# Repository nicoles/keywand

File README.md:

# keywand
 Key of the Star, with powers burning bright, reveal the staff and shine your light. RELEASE!

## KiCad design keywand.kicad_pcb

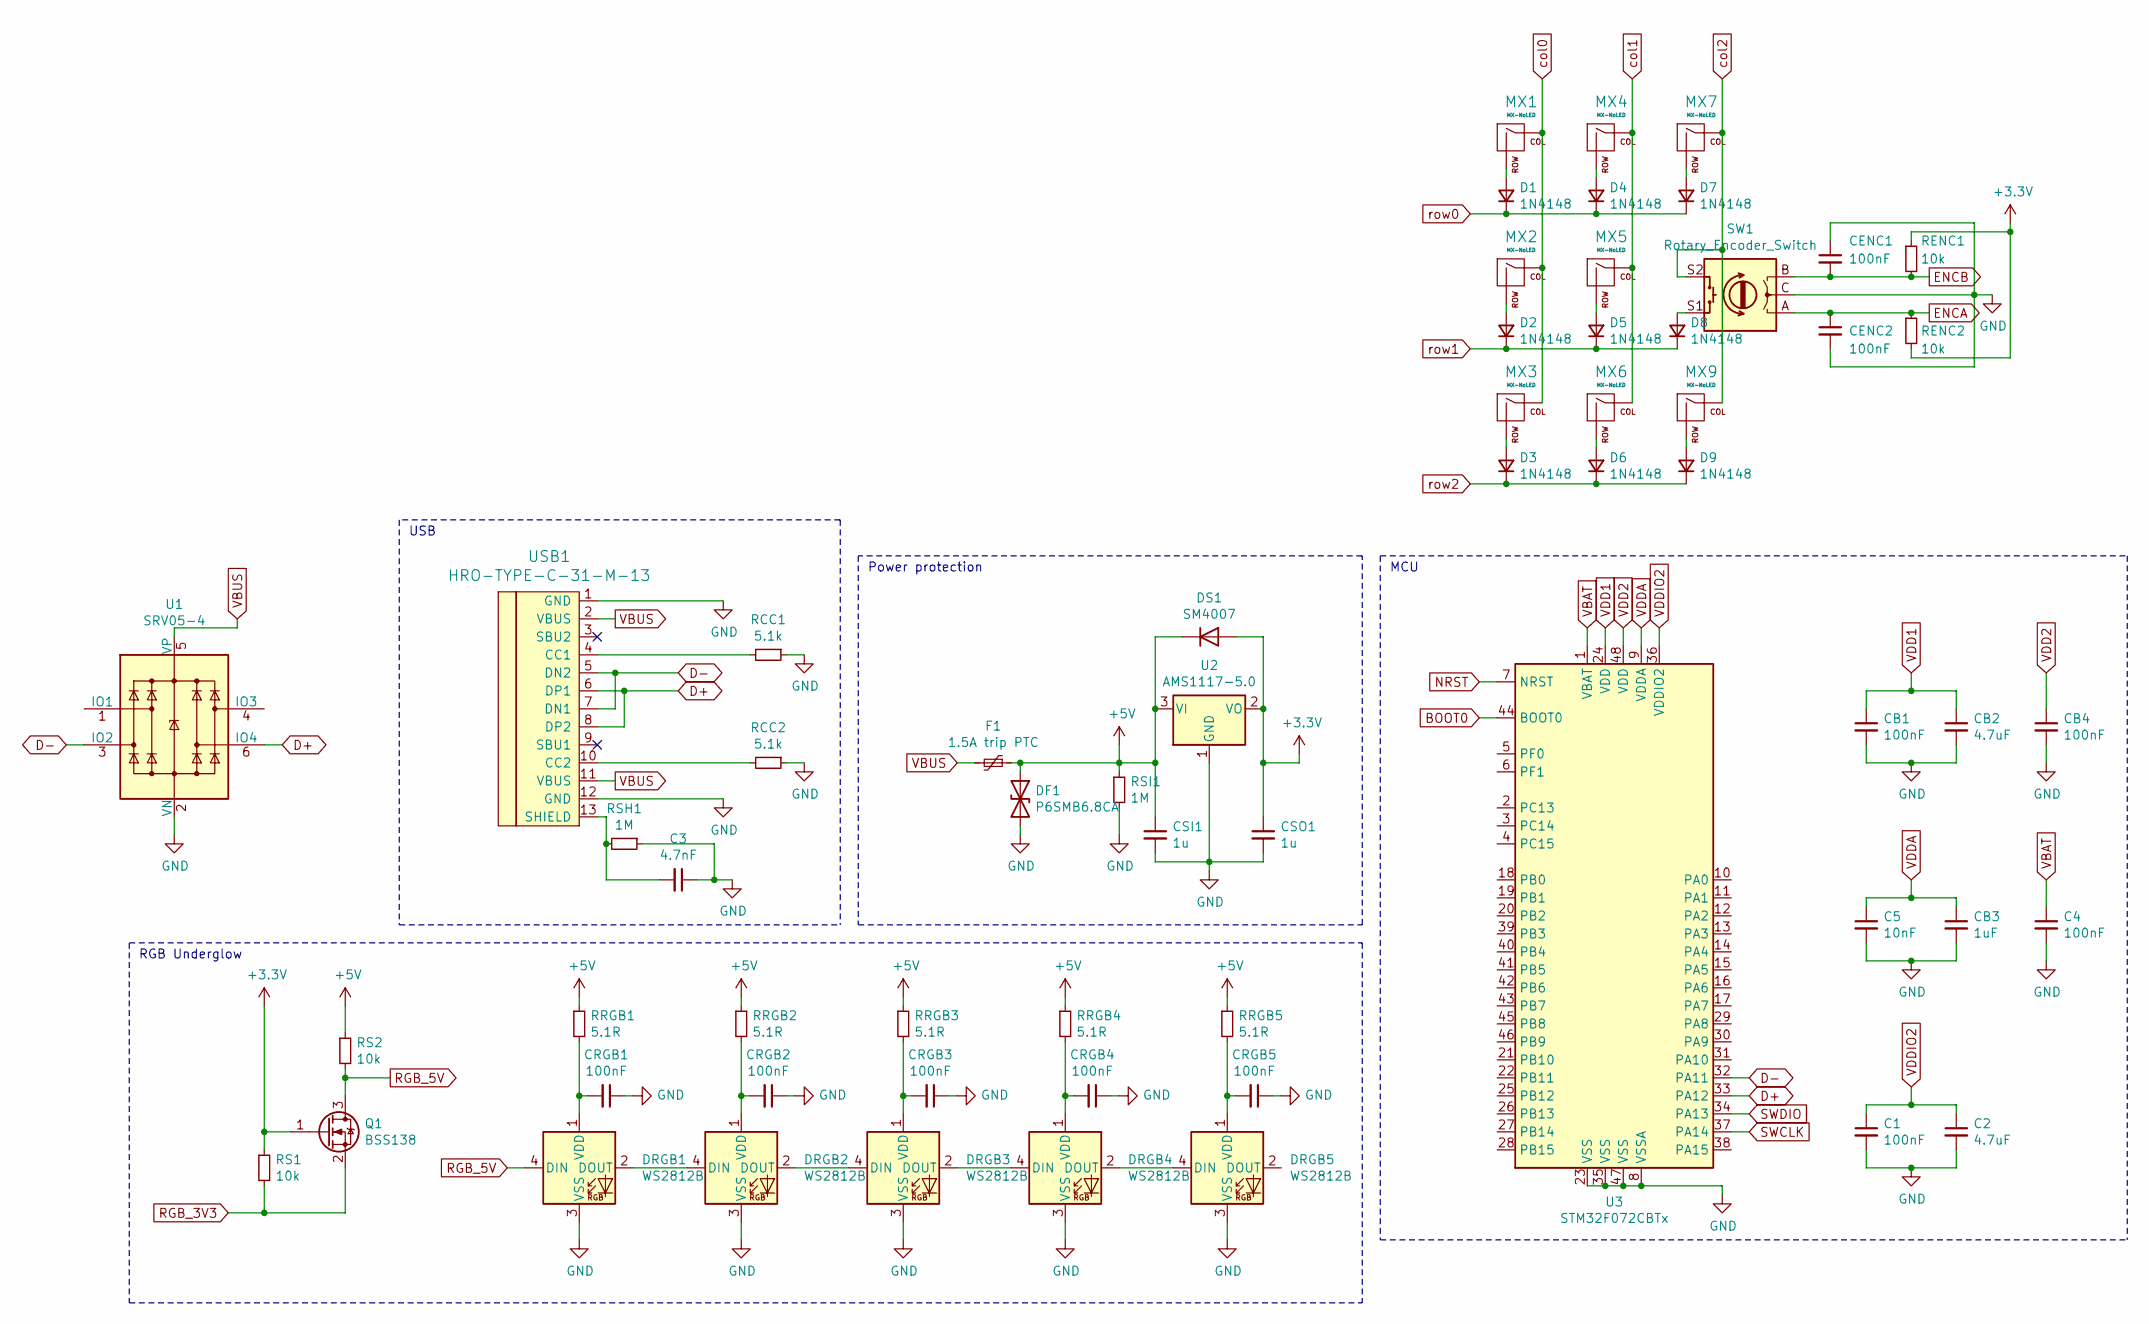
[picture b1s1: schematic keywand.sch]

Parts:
C1, C4: 100nF; C_0402_1005Metric; LCSC C1525
C2: 4.7uF; C_0402_1005Metric; LCSC C23733
C3: 4.7nF; C_0603_1608Metric; LCSC C53987
C5: 10nF; C_0402_1005Metric; LCSC C15195
CB1, CB4: 100nF; C_0402_1005Metric; LCSC C1525
CB2: 4.7uF; C_0402_1005Metric; LCSC C23733
CB3: 1uF; C_0402_1005Metric; LCSC C52923
CENC1, CENC2: 100nF; C_0603_1608Metric; LCSC C14663
CRGB1, CRGB2, CRGB3, CRGB4, CRGB5: 100nF; C_0603_1608Metric
CSI1: 1u; C_0805_2012Metric; JLCCode C28323
CSO1: 1u; C_0805_2012Metric; JLCCode C28323
D1, D2, D3, D4, D5, D6, D7, D8, D9: 1N4148; D_SOD-123; LCSC C81598
DF1: P6SMB6.8CA; D_SMB; JLCCode C78395
DRGB1, DRGB2, DRGB3, DRGB4, DRGB5: WS2812B; LED_SK6812MINI_PLCC4_3.5x3.5mm_P1.75mm; JLCCode C114583
DS1: SM4007; D_MELF; JLCCode C64898
F1: 1.5A trip PTC; Fuse_1812_4532Metric; JLCCode C84140
MX1, MX2, MX3, MX4, MX5, MX6, MX7, MX9: MX-NoLED; MXOnly-1U-NoLED
Q1: BSS138; SOT-23; JLCCode C193019
RCC1, RCC2: 5.1k; R_0603_1608Metric
RENC1, RENC2: 10k; C_0603_1608Metric; LCSC C25804
RRGB1, RRGB2, RRGB3, RRGB4, RRGB5: 5.1R; R_0603_1608Metric; JLCCode C25197
RS1, RS2: 10k; R_1206_3216Metric; JLCCode C17902
RSH1: 1M; R_0603_1608Metric
RSI1: 1M; C_0603_1608Metric; JLCCode C22935
SW1: Rotary_Encoder_Switch; RotaryEncoder_Alps_EC12E-Switch_Vertical_H20mm
U1: SRV05-4; SOT-23-6; LCSC C85364
U2: AMS1117-5.0; SOT-223-3_TabPin2; JLCCode C6187
U3: STM32F072CBTx; LQFP-48_7x7mm_P0.5mm
USB1: HRO-TYPE-C-31-M-13; LCSC C223906

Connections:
+3V3: CSO1.1, DS1.2 (A), Q1.1 (G), RENC1.1, RENC2.2, RS1.1, U2.2 (VO)
+5V: CSI1.1, DF1.1 (A1), DS1.1 (K), F1.1, RRGB1.1, RRGB2.1, RRGB3.1, RRGB4.1, RRGB5.1, RS2.1, RSI1.1, U2.3 (VI)
BOOT0: U3.44 (BOOT0)
D+: U1.6 (IO4), U3.33 (PA12), USB1.6 (DP1), USB1.8 (DP2)
D-: U1.3 (IO2), U3.32 (PA11), USB1.5 (DN2), USB1.7 (DN1)
ENCA: CENC2.1, RENC2.1, SW1.A
ENCB: CENC1.2, RENC1.2, SW1.B
GND: C1.2, C2.2, C3.1, C4.2, C5.2, CB1.2, CB2.2, CB3.2, CB4.2, CENC1.1, CENC2.2, CRGB1.1, CRGB2.1, CRGB3.1, CRGB4.1, CRGB5.1, CSI1.2, CSO1.2, DF1.2 (A2), DRGB1.3 (VSS), DRGB2.3 (VSS), DRGB3.3 (VSS), DRGB4.3 (VSS), DRGB5.3 (VSS), RCC1.1, RCC2.1, RSH1.1, RSI1.2, SW1.C, U1.2 (VN), U2.1 (GND), U3.8 (VSSA), U3.23 (VSS), U3.35 (VSS), U3.47 (VSS), USB1.1 (GND), USB1.12 (GND)
NRST: U3.7 (NRST)
unnamed: C3.2, RSH1.2, USB1.13 (SHIELD)
unnamed: CRGB1.2, DRGB1.1 (VDD), RRGB1.2
unnamed: CRGB2.2, DRGB2.1 (VDD), RRGB2.2
unnamed: CRGB3.2, DRGB3.1 (VDD), RRGB3.2
unnamed: CRGB4.2, DRGB4.1 (VDD), RRGB4.2
unnamed: CRGB5.2, DRGB5.1 (VDD), RRGB5.2
unnamed: D1.2 (A), MX1.2 (ROW)
unnamed: D2.2 (A), MX2.2 (ROW)
unnamed: D3.2 (A), MX3.2 (ROW)
unnamed: D4.2 (A), MX4.2 (ROW)
unnamed: D5.2 (A), MX5.2 (ROW)
unnamed: D6.2 (A), MX6.2 (ROW)
unnamed: D7.2 (A), MX7.2 (ROW)
unnamed: D8.2 (A), SW1.S1
unnamed: D9.2 (A), MX9.2 (ROW)
unnamed: DRGB1.2 (DOUT), DRGB2.4 (DIN)
unnamed: DRGB2.2 (DOUT), DRGB3.4 (DIN)
unnamed: DRGB3.2 (DOUT), DRGB4.4 (DIN)
unnamed: DRGB4.2 (DOUT), DRGB5.4 (DIN)
unnamed: RCC1.2, USB1.4 (CC1)
unnamed: RCC2.2, USB1.10 (CC2)
RGB_3V3: Q1.2 (S), RS1.2
RGB_5V: DRGB1.4 (DIN), Q1.3 (D), RS2.2
SWCLK: U3.37 (PA14)
SWDIO: U3.34 (PA13)
VBAT: C4.1, U3.1 (VBAT)
VBUS: F1.2, U1.5 (VP), USB1.2 (VBUS), USB1.11 (VBUS)
VDD1: CB1.1, CB2.1, U3.24 (VDD)
VDD2: CB4.1, U3.48 (VDD)
VDDA: C5.1, CB3.1, U3.9 (VDDA)
VDDIO2: C1.1, C2.1, U3.36 (VDDIO2)
col0: MX1.1 (COL), MX2.1 (COL), MX3.1 (COL)
col1: MX4.1 (COL), MX5.1 (COL), MX6.1 (COL)
col2: MX7.1 (COL), MX9.1 (COL), SW1.S2
row0: D1.1 (K), D4.1 (K), D7.1 (K)
row1: D2.1 (K), D5.1 (K), D8.1 (K)
row2: D3.1 (K), D6.1 (K), D9.1 (K)

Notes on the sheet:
MCU
Power protection
RGB Underglow
USB

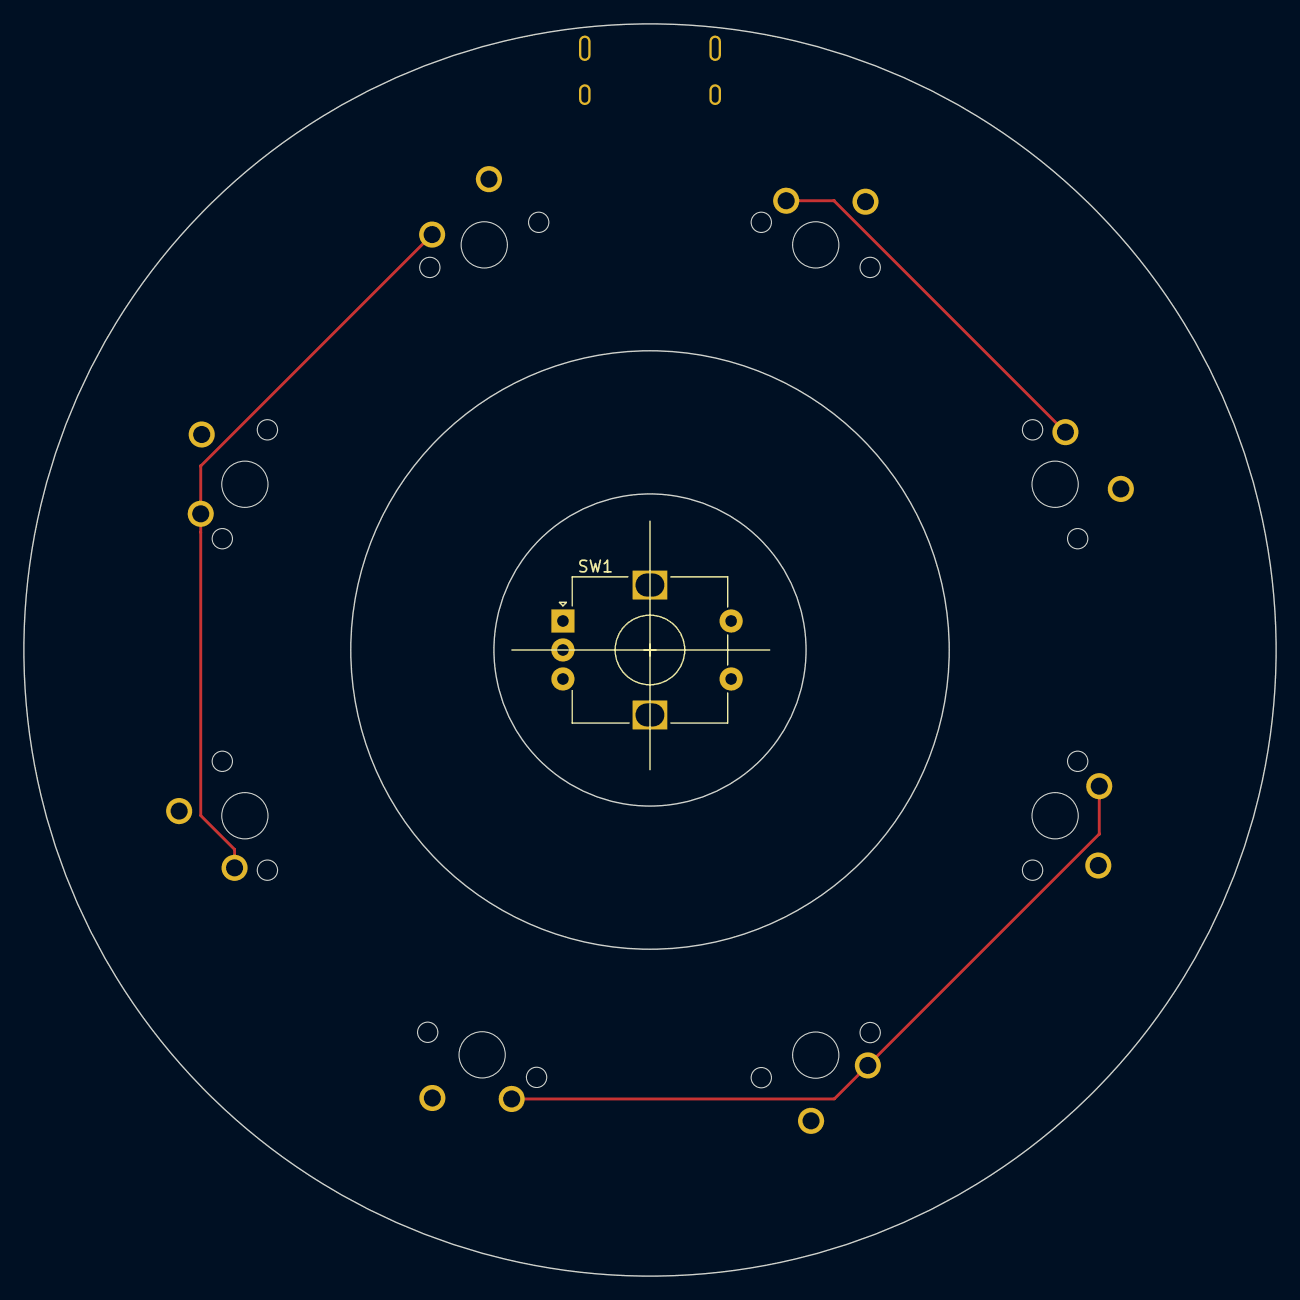
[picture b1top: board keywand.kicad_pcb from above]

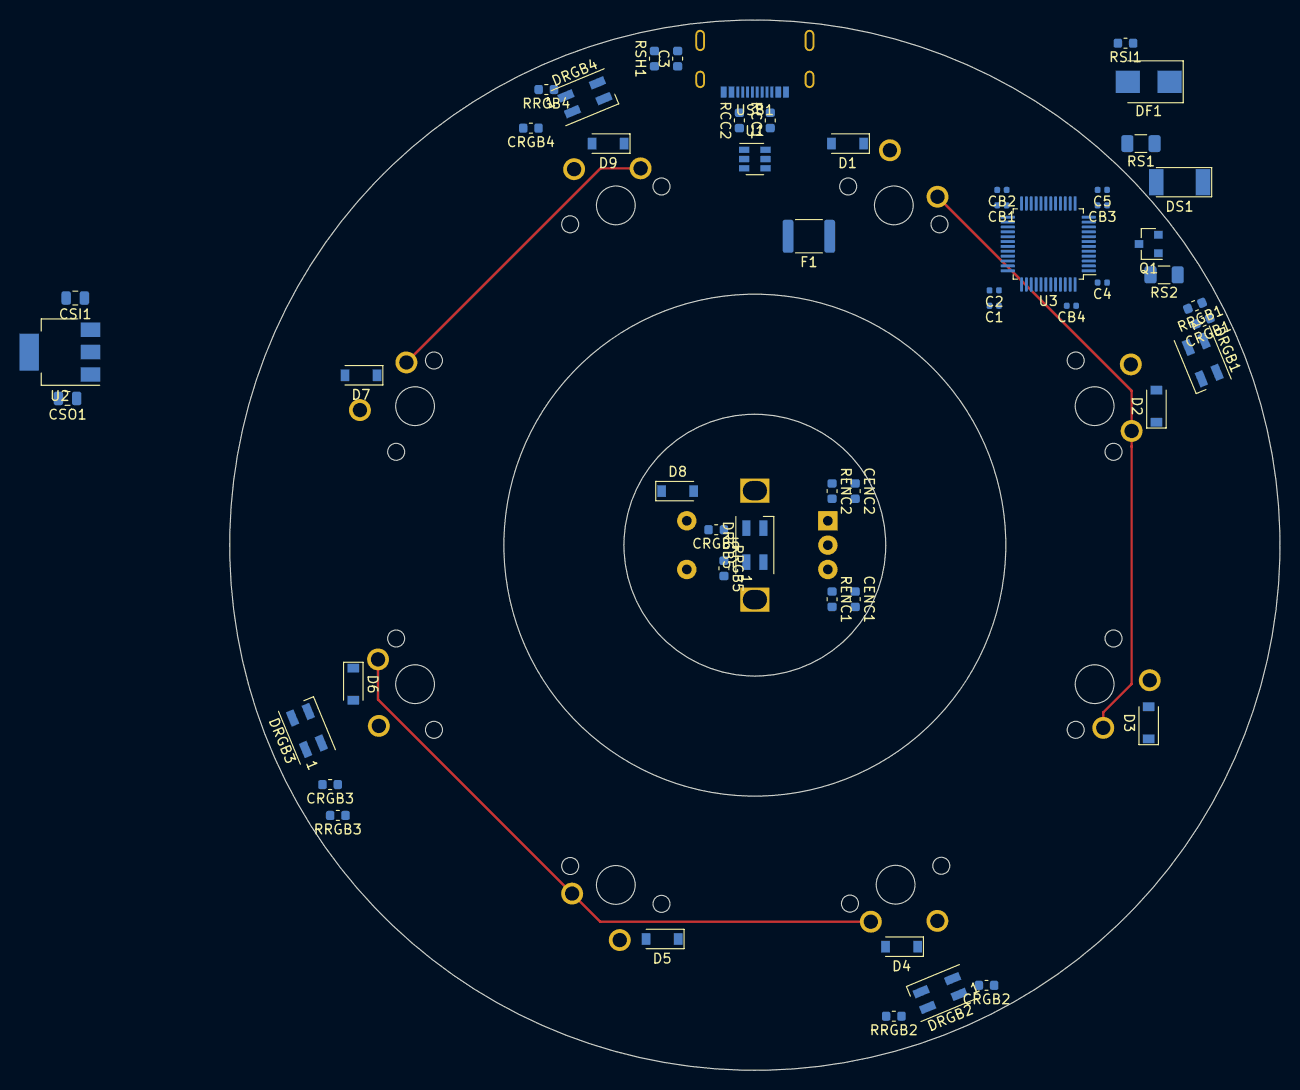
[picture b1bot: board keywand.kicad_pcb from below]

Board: 2 copper layers, 107.9 x 107.9 mm, 62 parts (53 on the bottom side), 42 nets.

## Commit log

2020-07-04 Empty kicad project
2020-07-04 added submodules
2020-07-04 added mx & keeb bits libraries
2020-07-04 matrix and mcu get!
2020-07-04 Added type-c submodule
2020-07-04 Now with more usb-c!
2020-07-04 Updated layout just so it's a little easier to parse. more boxes to come
2020-07-05 Added rgb underglow
2020-07-06 Started layout of board!
